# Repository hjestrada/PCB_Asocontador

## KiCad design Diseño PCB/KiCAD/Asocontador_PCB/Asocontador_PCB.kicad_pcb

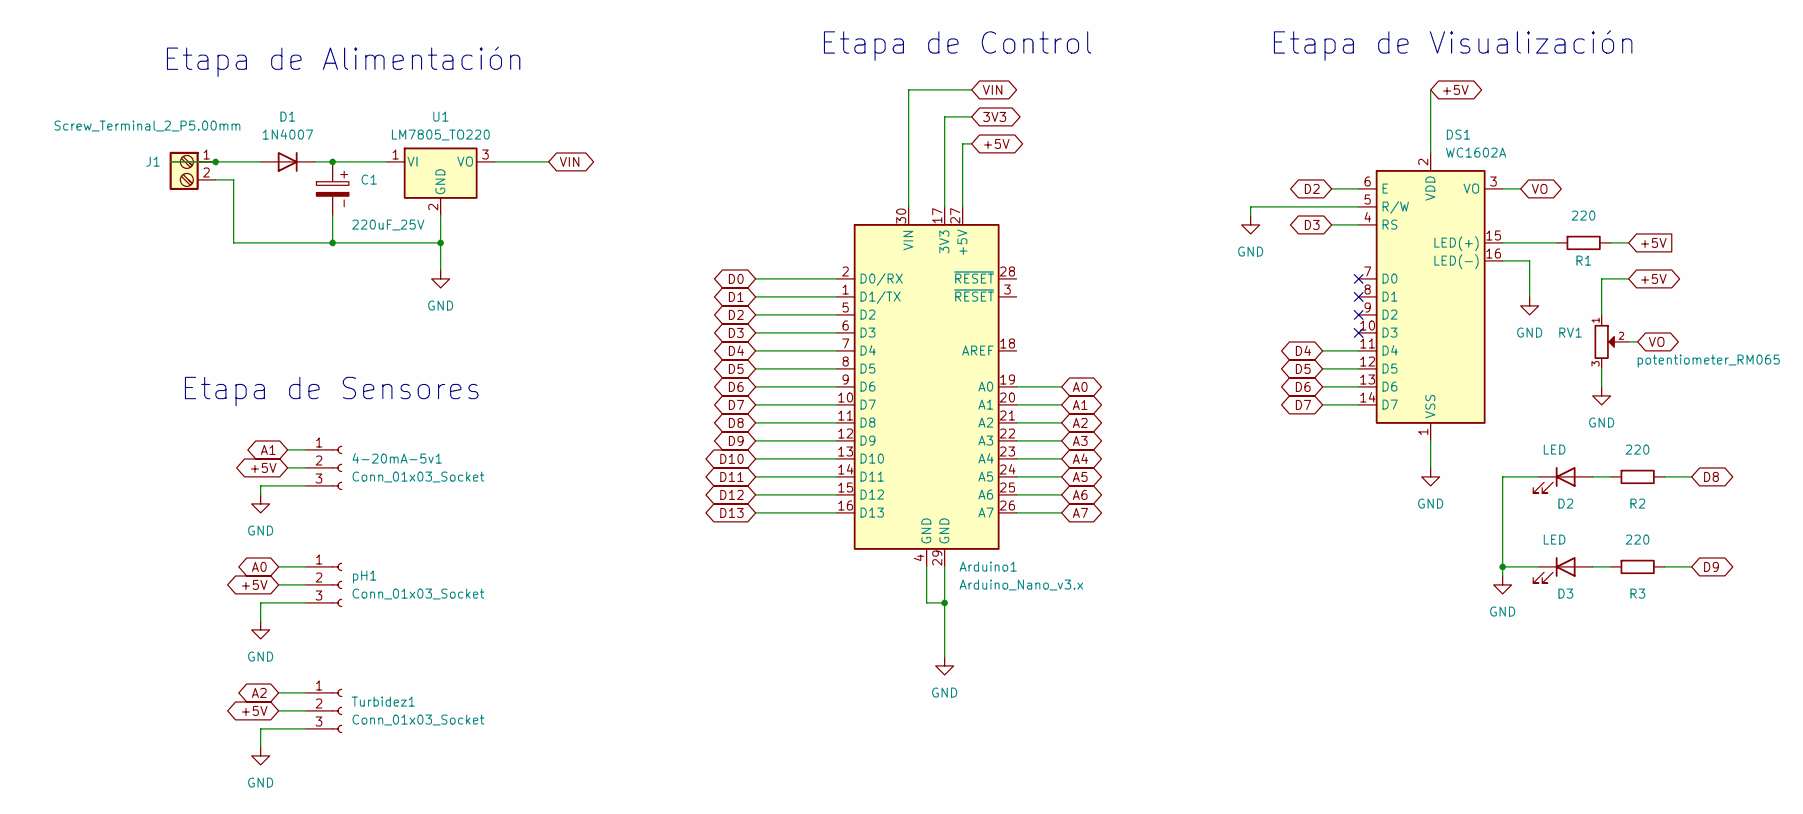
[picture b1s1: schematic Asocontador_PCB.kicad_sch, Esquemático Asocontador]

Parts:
4-20mA-5v1: Conn_01x03_Socket; JST_EH_B3B-EH-A_1x03_P2.50mm_Vertical
Arduino1: Arduino_Nano_v3.x; Arduino_Nano
C1: 220uF_25V; CP_Radial_D8.0mm_P3.50mm
D1: 1N4007; D_DO-41_SOD81_P10.16mm_Horizontal
D2, D3: LED; LED_D3.0mm
DS1: WC1602A
J1: Screw_Terminal_2_P5.00mm; TerminalBlock_Phoenix_PT-1,5-2-5.0-H_1x02_P5.00mm_Horizontal
R1, R2, R3: 220; R_Axial_DIN0207_L6.3mm_D2.5mm_P10.16mm_Horizontal
RV1: potentiometer_RM065; Potentiometer_RM065
Turbidez1: Conn_01x03_Socket; JST_EH_B3B-EH-A_1x03_P2.50mm_Vertical
U1: LM7805_TO220; TO-220F-3_Horizontal_TabDown
pH1: Conn_01x03_Socket; JST_EH_B3B-EH-A_1x03_P2.50mm_Vertical

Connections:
3V3: Arduino1.17 (3V3)
+5V: 4-20mA-5v1.2, Arduino1.27 (+5V), DS1.2 (VDD), R1.2, RV1.1, Turbidez1.2, pH1.2
A0: Arduino1.19 (A0), pH1.1
A1: 4-20mA-5v1.1, Arduino1.20 (A1)
A2: Arduino1.21 (A2), Turbidez1.1
A3: Arduino1.22 (A3)
A4: Arduino1.23 (A4)
A5: Arduino1.24 (A5)
A6: Arduino1.25 (A6)
A7: Arduino1.26 (A7)
D0: Arduino1.2 (D0/RX)
D1: Arduino1.1 (D1/TX)
D2: Arduino1.5 (D2), DS1.6 (E)
D3: Arduino1.6 (D3), DS1.4 (RS)
D4: Arduino1.7 (D4), DS1.11 (D4)
D5: Arduino1.8 (D5), DS1.12 (D5)
D6: Arduino1.9 (D6), DS1.13 (D6)
D7: Arduino1.10 (D7), DS1.14 (D7)
D8: Arduino1.11 (D8), R2.2
D9: Arduino1.12 (D9), R3.2
D10: Arduino1.13 (D10)
D11: Arduino1.14 (D11)
D12: Arduino1.15 (D12)
D13: Arduino1.16 (D13)
GND: 4-20mA-5v1.3, Arduino1.4 (GND), Arduino1.29 (GND), C1.2, D2.1 (K), D3.1 (K), DS1.1 (VSS), DS1.5 (R/W), DS1.16 (LED(-)), J1.2, RV1.3, Turbidez1.3, U1.2 (GND), pH1.3
unnamed: D1.2 (A), J1.1
unnamed: C1.1, D1.1 (K), U1.1 (VI)
unnamed: D2.2 (A), R2.1
unnamed: D3.2 (A), R3.1
unnamed: DS1.15 (LED(+)), R1.1
VIN: Arduino1.30 (VIN), U1.3 (VO)
VO: DS1.3 (VO), RV1.2

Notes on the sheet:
Etapa de Sensores
Etapa de Visualización
Etapa de Alimentación
Etapa de Control

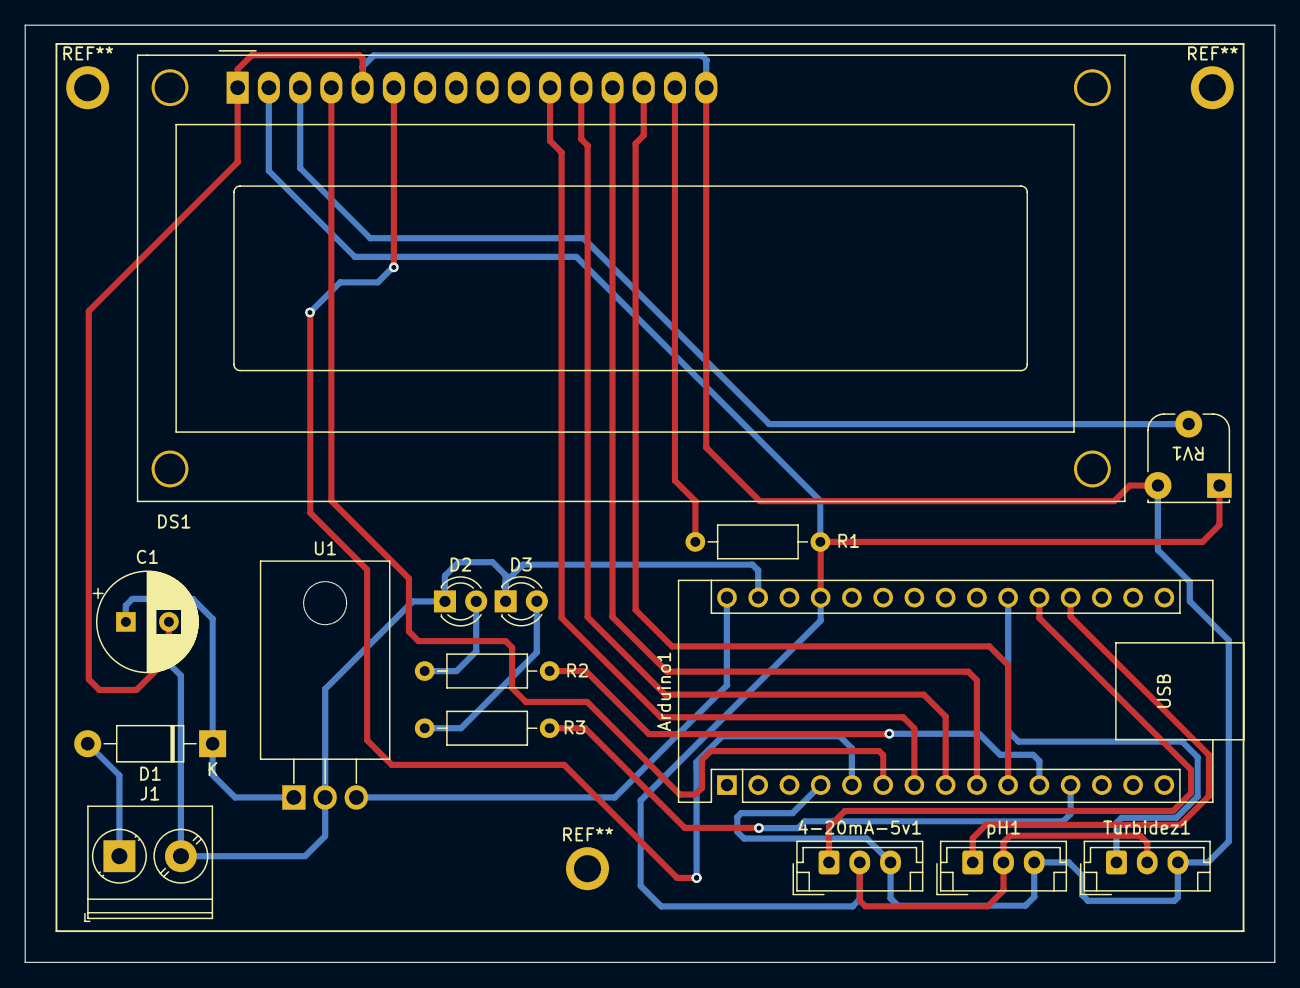
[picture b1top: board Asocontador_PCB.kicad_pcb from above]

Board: 2 copper layers, 101.6 x 76.2 mm, 15 parts (0 on the bottom side), 20 nets.

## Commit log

2023-09-27 Cambios Iniciales
2023-09-27 Modificaciones Varias
2023-09-28 Cambios varios
2023-10-06 cxzc
2023-10-10 Cambios
2023-11-04 Funcionando MQTT
2023-11-04 Modificaciones
2023-11-20 Muchos cambios, sensores calibrados
2023-11-28 algo
2024-02-07 CAmibios
